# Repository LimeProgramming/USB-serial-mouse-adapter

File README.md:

# USB Serial Mouse Adapter
A USB to serial mouse adapter!

## About
This project came about when I got my hands on an old 486 based PC. Having never really dipped my toes into retro computing, I didn't have an old serial mouse on hand. A quick eBay searched revealed that the decent ones cost a nice chunk of change that I didn't feel they were worth. Another search on Vogons revealed that some mad lads out there made active PS/2 to serial adapters using various micro controllers.  
Out of curiosity I examined how these worked and thought "Why can't I do this with a Pi Pico and USB mouse?" which kicked off this project. 

I hope it sparks your interest!
-Lime

## Features
With this adapter you can convert a modern native USB mouse to a classic serial mouse. That's right, native USB! No cheating by secretly using PS/2 compatible mice.
Want to use an optical mouse on a 386 running Wolfenstein 3D? Well now you can! Want to use a wireless optical mouse on a 486 running Doom? Well you might be able to! (depending on the mouse)

**Supported Protocols:**
- Microsoft Two Button
- Logitech Three Button
- Microsoft Wheel

**Unsupported Protocols: (May change based on demand)**
- Mousesystems
- Sun
- MM

### KVM:
Support for use on KVMs has been added as of version 1.1.1. 
It works fine on my **one**, startech branded, KVM that I have test with. Given that TinyUSB is a bit picky, your results may vary.

## PCBs
There are two variants of the PCB available in the KiCad folder, Phat and Slim for your preference. The main circuit for both PCBs is the same so the firmware package will work on both PCBs. A full BOM for LCSC (except for header pins) is available in the Phat folder: [LCSC BOM](https://raw.githubusercontent.com/LimeProgramming/USB-serial-mouse-adapter/main/KiCad/Phat/BOM_LCSC.xls). For the Slim build you can omit the dip switches and reset switch (you will have to source an appropriate SMD reset switch).

### Building a PCB:

#### MAX232/3232 voltage selection:
The PCB has a jumper to select between 3.3v and 5v for the MAX chip. 
- If you're using a MAX232 then bridge 5v to the center pin and install all the resistors. The part listed in the [BOM](https://raw.githubusercontent.com/LimeProgramming/USB-serial-mouse-adapter/main/KiCad/Phat/BOM_LCSC.xls) is a MAX232 chip.
- If you're using a MAX3232 then bridge 3.3v to the center pin, bridge R4 and R3, and remove R1 and R2.

#### Board to Pico USB data connection:
The `TP2` and `TP3` testpoints on the board must be soldered to the corresponding `TP2` and `TP3` test points on the Pico, underneath the USB connector:

### Phat:

Also known as the original design.
This PCB is the version I had made with the mindset of it being the default/one and only. 
| Differences | Silkscreen | Description |
|:--:|:--:| :--:|
| Serial Pin Header | J1 | Intended to use with a serial breakout cable |
| USB Pin Header | J3 | Intended to be used with motherboard USB breakout cables |
| Dip Switches | SW1 | Quickly and easily configure the adapter |

#### Phat Cases:

### Slim:

Made for people be require the adapter to be as small as possible. Not much wider than the serial port itself. 

## Powering the device
### MicroUSB:

The easiest way to power the device would be to use the Pico's micro USB port. Be sure to use a USB power only cable or a wall power adapter otherwise it won't pick up the mouse.

**PLEASE NOTE:** Some "power only" USB cables have the data lines shorted together. You can test if this is the case by plugging the cable into the Pico and using a meter to check for continuity between `TP2` and `TP3` on the Pico. If there is continuity you have a cable like this. Cut the data lines on a normal USB cable as an option.
<br clear="left"/>

### Power-In Header:

Both the Phat and Slim PCB's feature an 5 volt power in header. You can use this creatively to power the adapter, even from the PC itself perhaps? Personally I'm connecting it to a wall power supply to give a more secure connection than MicroUSB.
<br clear="left"/>

### Other ways:
There is nothing stopping you from powering the device using a powered OTG cable or a hacked up USB extension lead. The device itself needs about 100 milliamps so as long as you get it that power, it'll run away happily!

## Configuration

The adapter has quite a few settings available and these settings are stored on micro controllers flash memory. 
It will remember your settings between uses and the same settings carry between different computers and even firmware upgrades (unless otherwise state in a changes log)

There are two primary ways of editing the settings of the USB-2-232

### Headers
The phat variant of the PCB includes headers in either of the form of dip switches or jumper headers. While not super configurable they do give quick access to some handy settings. The headers can be set while the micro controller is on with changes being applied in real-time or they can be set while the micro controller is off with changes being applied next time the controller is booted.

| Num | Setting |
|:--:|:--:|
| 1 | Three Button Logitech Protocol |
| 2 | MS Wheel Protocol |
| 3 | 75% Mouse Travel Modifier / Dip 3 + 4 for 25% |
| 4 | 50% Mouse Travel Modifier / Dip 3 + 4 for 25% |
| 5 | 7N2|
| 6 | 19200 Baud Rate|

### Serial Terminal

Both the phat and slim variants of the PCB support being configured via serial terminal. The serial terminal allows for more advanced configuration of the mouse adapter. Any additional settings added in a software update will be available here.
The serial terminal has been translated to German, images available in both German and English as default langauge.  

### Serial Terminal Options
+ Mouse Travel
    + List Config
            | List the current mouse travel settings
    + XY Travel 
            | XY mouse travel modifier 1% -> 200%
    + X Travel
             | X (Left and Right) mouse travel modifier 1% -> 200%
    + Y Travel 
            | Y ( Up and Down) mouse travel modifier 1% -> 200%
    + Invert X
            | Invert X (Left and Right) mouse movement.
    + Invert Y
            | Invert Y (Up and Down) mouse movement.
    + Movement Type
            | Set Movement Type. USB mice talk faster than serial mice, movement type decides what to do with the backlog between serial mouse updates.
        + Additive: 
                | Sum the mouse movement (Sensitive)
        + Average
                | Avg the mouse movement  (Insensitive)
        + Coast 
                | Send the mouse movement incrementally (Slippy)
    + Cosine Smoothing
            | Makes the cursor proportionally less sensitive at high speeds, leaving the movement mostly one to one at low speeds

+ Mouse Buttons
    + List Config
        | List the current mouse button settings
    + Swap Left and Right
        | Swap the left and right mouse buttons
    + Use Forward and Backward
        | Use the mouse forward and back buttons as alternative left and right buttons
    + Swap Forward and Backward
        | Swap forward and back buttons if they are being used as alternative left and right buttons
+ Serial Settings
    + List Config
        | List the current serial settings
    + Format
        | One stop bit (7N1) or two stop bits (7N2) 
    + Baud Rate
        | 1200 2400 4800 9600 19200 Baud Rates. Note you will need compatible mouse drivers.
     + Mouse Type
     | Microsoft 2 Button, Logitech Three Button or Microsoft Wheel mouse. Note: You may need to reconfigure your mouse driver upon change.
+ Firmware
    + Information | Information about the firmware
    + Language | Set the language of the settings terminal
    + Reset | Reset mouse settings back to default
    + List Default Settings | List the default settings of the adapter
+ Exit
    + Return to mouse mode

### Accessing the terminal
You can access the serial terminal in one of two ways:

#### Method 1: Serial Terminal Emulator
You can open a serial terminal emulator (like kermit) on the computer you have the mouse connected to, connect to the same com port the mouse driver is using and press the enter key.
```
Baud Rate: User Set
Data Bits: 7
Stop Bits: User Set
Parity: None
Flow Control: None
```
#### Method 2: USB to TTL
You can also connect the unused UART of the Pi Pico with a cheap USB to TTL device or even another Pico running the picoprobe firmware. Open your favorite serial terminal emulator (like putty) connect to the TTL device and tap the enter key. 
```
Baud Rate: 115200
Data Bits: 8
Stop Bits: 1
Parity: None
Flow Control: None
```
Connecting to the adapter in this way will allow you to change settings regardless of the adapter being connected to a PC or not. 
The unused UART of the pico can be accessed from the top two pins between the full size USB port of the PCB and the micro USB port of the Pico.

### Resetting the adapter
Forgot your settings and can't get the adapter working? Don't worry.
There are three different ways to reset the adapter:

#### --- Serial Terminal
As written above, you can reset the adapter back to default settings from the terminal. You can connect to the unused UART of the pico regardless of the settings of the mouse. 

#### --- Small Flat Head Screwdriver

**How To:**
1. Press a small flat head into the position shown above.
2. Power on the adapter and the Picos built-in LED will glow solid.
3. Hold the flat head in position for two or three seconds for the Picos LED to start blinking.
4. Once it is blinking, you can let go of the GPIO and press the reset button.
5. The adapter will boot up with default settings.
#### --- Nuke UF2
**How To:**
1. Download the [flash_nuke.uf2](https://datasheets.raspberrypi.com/soft/flash_nuke.uf2) file.
2. Connect the adapter to your PC using the microusb port built into the Pi Pico.
3. Hold Reset, then bootsel, then release reset then bootsel. This will make the Pico appear as a removable storage device. 
4. Drag the flash_nuke.uf2 file to the storage device. This will reset the flash the on the Pi Pico.
5. The Pico should reboot on its own and show up as a removable storage device again. If it doesn't, tap the reset button.
6. Download the latest firmware and drag that UF2 file to the storage device.
7. The adapter will boot up with default settings.

# Compiling the Firmware
The default mouse settings can be edited in `default_config.h` prior to compilation. You can use this to set the mouses default settings for your own configuration. 

The build environment is a normal PicoSDK setup, there are several guides out the for both Linux and Windows.  From experience the setup is easier in Linux. However there is one important thing you need to know:

**PicoSDK Version 1.5.1**
Previous Versions of this project required a customized version of TinyUSB, since then TinyUSB has implemented improved USB HUB and Hosting functions so the customized TinyUSB is no longer required. 
However, TinyUSB version 16 is recommended for the scroll wheel to work more reliably. 

# Known Issues
**USB Hubs**
Due to the pico having a USB 1.1 host or TinyUSB not using hubs correctly, this project struggles with hub compatibility. 
A hub which should work but I have not texted can be found here: https://www.olimex.com/Products/USB-Modules/USB-NeoHub/open-source-hardware 

Personally I use an amazon basics 4 port USB2.0 hub and it works perfectly.

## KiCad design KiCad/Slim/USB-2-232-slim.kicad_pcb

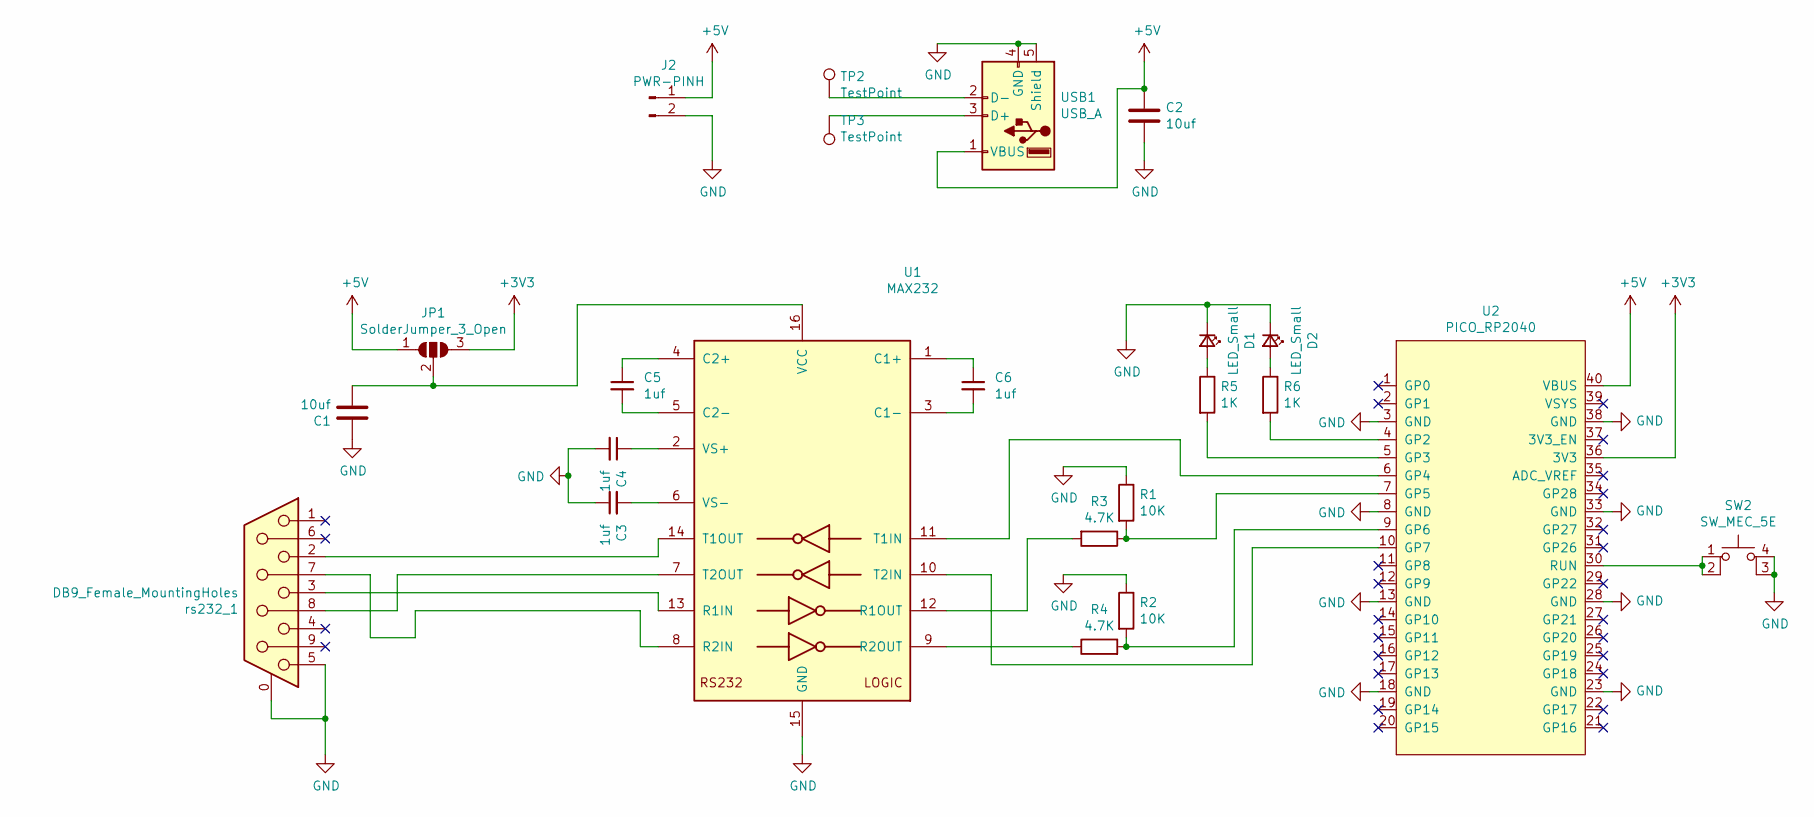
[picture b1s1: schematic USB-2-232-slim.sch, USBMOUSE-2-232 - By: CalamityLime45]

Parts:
C1, C2: 10uf; C_0805_2012Metric
C3, C4, C5, C6: 1uf; C_0805_2012Metric
D1, D2: LED_Small; LED_D3.0mm
J2: PWR-PINH; PinSocket_1x02_P2.54mm_Vertical
JP1: SolderJumper_3_Open; SolderJumper-3_P1.3mm_Open_Pad1.0x1.5mm_NumberLabels
R1, R2: 10K; R_0805_2012Metric
R3: 4.7K; R_0805_2012Metric_bridge
R4: 4.7K; R_0805_2012Metric_bridgeflip
R5, R6: 1K; R_0805_2012Metric
SW2: SW_MEC_5E; SMT_RESET_SW
TP2, TP3: TestPoint; TestPoint_Pad_1.5x1.5mm
U1: MAX232; max232_SMD
U2: PICO_RP2040; RPi_Pico_SMD_TH
USB1: USB_A; USB_A_Wuerth_614004134726_Horizontal
rs232_1: DB9_Female_MountingHoles; DSUB-9_Female_Horizontal_P2.77x2.84mm_EdgePinOffset7.70mm_H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

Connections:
+3V3: JP1.3 (B), U2.36 (3V3)
+5V: C2.1, J2.1, JP1.1 (A), U2.40 (VBUS), USB1.1 (VBUS)
GND: C1.1, C2.2, C3.1, C4.2, D1.1 (K), D2.1 (K), J2.2, R1.1, R2.1, SW2.3 (K), SW2.4 (A), U1.15 (GND), U2.3 (GND), U2.8 (GND), U2.13 (GND), U2.18 (GND), U2.23 (GND), U2.28 (GND), U2.33 (GND), U2.38 (GND), USB1.4 (GND), USB1.5 (Shield), rs232_1.0 (PAD), rs232_1.5
unnamed: C1.2, JP1.2 (C), U1.16 (VCC)
unnamed: C3.2, U1.6 (VS-)
unnamed: C4.1, U1.2 (VS+)
unnamed: C5.1, U1.4 (C2+)
unnamed: C5.2, U1.5 (C2-)
unnamed: C6.1, U1.1 (C1+)
unnamed: C6.2, U1.3 (C1-)
unnamed: D1.2 (A), R5.1
unnamed: D2.2 (A), R6.1
unnamed: R1.2, R3.1, U2.7 (GP5)
unnamed: R2.2, R4.2, U2.9 (GP6)
unnamed: R3.2, U1.12 (R1OUT)
unnamed: R4.1, U1.9 (R2OUT)
unnamed: R5.2, U2.5 (GP3)
unnamed: R6.2, U2.4 (GP2)
unnamed: SW2.1, SW2.2, U2.30 (RUN)
unnamed: TP2.1, USB1.2 (D-)
unnamed: TP3.1, USB1.3 (D+)
unnamed: U1.7 (T2OUT), rs232_1.8
unnamed: U1.8 (R2IN), rs232_1.7
unnamed: U1.10 (T2IN), U2.10 (GP7)
unnamed: U1.11 (T1IN), U2.6 (GP4)
unnamed: U1.13 (R1IN), rs232_1.3
unnamed: U1.14 (T1OUT), rs232_1.2

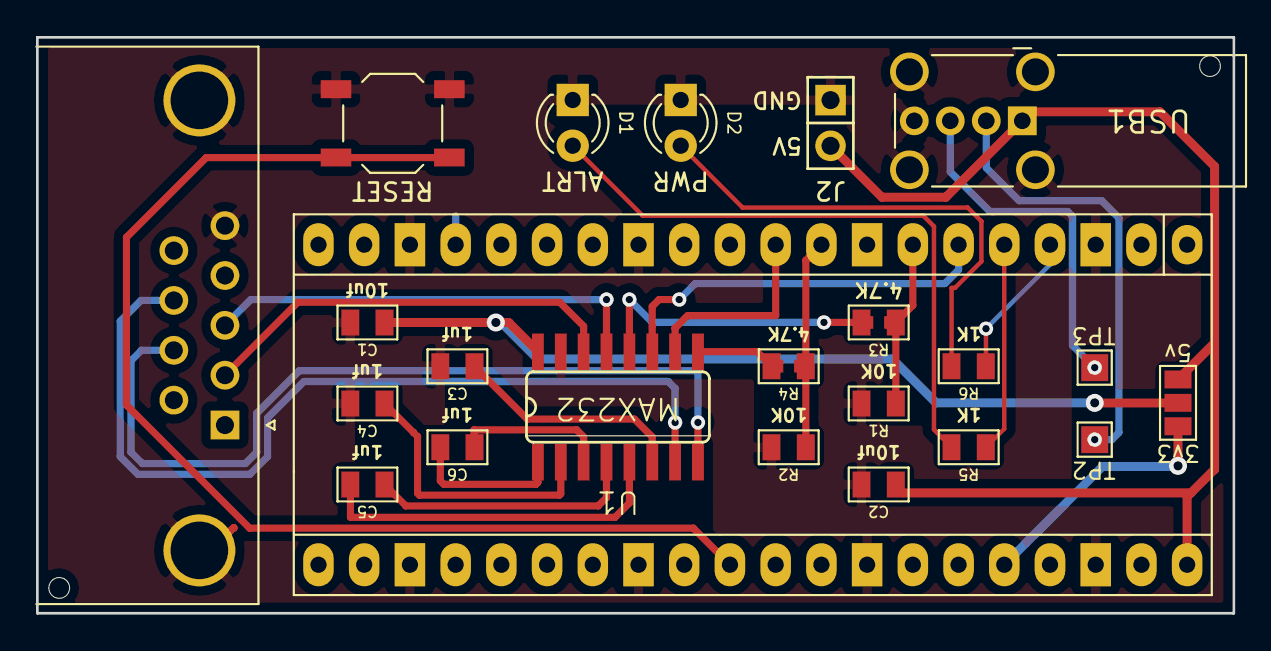
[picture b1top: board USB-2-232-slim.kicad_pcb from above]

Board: 2 copper layers, 66.5 x 32.0 mm, 23 parts (0 on the bottom side), 27 nets.

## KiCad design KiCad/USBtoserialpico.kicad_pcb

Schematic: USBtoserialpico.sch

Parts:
C1, C2, C3, C5: 1uf; C_1206_3216Metric
C4, C6: 10uf; C_1206_3216Metric
D1, D2: LED_Small; LED_D3.0mm
J1: Conn_01x04_Male; Serial_PinSocket_1x04_P2.54mm
J2: Conn_01x02_Male; PinSocket_1x02_P2.54mm_Vertical
J3: Conn_01x05_Male; PinSocket_1x05_P2.54mm_Vertical
JP1: SolderJumper_3_Open; SolderJumper-3_P1.3mm_Open_Pad1.0x1.5mm_NumberLabels
R1, R2: 3K; R_1206_3216Metric
R3, R4: R; R_1206_3216Metric
RB1: 1.5K; R_1206_3216Metric_bridge
RB2: 1.5K; R_1206_3216Metric
SW1: SW_DIP_x06; SW_DIP_SPSTx06_Slide_9.78x17.42mm_W7.62mm_P2.54mm
SW2: SW_MEC_5E; SW_PUSH_6mm
TP1, TP2: TestPoint; TestPoint_Pad_1.5x1.5mm
U1: MAX232; max232_SMD
U2: PICO_RP2040; RPi_Pico_SMD_TH
USB1: USB_A; USB_A_Wuerth_614004134726_Horizontal
rs232_1: DB9_Female_MountingHoles; DSUB-9_Male_Horizontal_P2.77x2.84mm_EdgePinOffset7.70mm_Hou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

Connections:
+5V: C6.1, J2.1, J3.1, JP1.1 (A), U2.40 (VBUS), USB1.1 (VBUS)
GND: C1.2, C2.1, C4.1, C6.2, J1.4, J2.2, J3.4, J3.5, R1.1, R2.1, R3.1, R4.1, SW1.7, SW1.8, SW1.9, SW1.10, SW1.11, SW1.12, SW2.3 (K), SW2.4 (A), U1.15 (GND), U2.3 (GND), U2.8 (GND), U2.13 (GND), U2.18 (GND), U2.23 (GND), U2.28 (GND), U2.33 (GND), U2.38 (GND), USB1.4 (GND), USB1.5 (Shield), rs232_1.5
unnamed: C1.1, U1.2 (VS+)
unnamed: C2.2, U1.6 (VS-)
unnamed: C3.1, U1.4 (C2+)
unnamed: C3.2, U1.5 (C2-)
unnamed: C4.2, JP1.2 (C), U1.16 (VCC)
unnamed: C5.1, U1.1 (C1+)
unnamed: C5.2, U1.3 (C1-)
unnamed: D1.1 (K), R3.2
unnamed: D1.2 (A), U2.5 (GP3)
unnamed: D2.1 (K), R4.2
unnamed: D2.2 (A), U2.4 (GP2)
unnamed: J1.1, U1.8 (R2IN), rs232_1.7
unnamed: J1.2, U1.13 (R1IN), rs232_1.2
unnamed: J1.3, U1.14 (T1OUT), rs232_1.3
unnamed: J3.2, TP1.1, USB1.2 (D-)
unnamed: J3.3, TP2.1, USB1.3 (D+)
unnamed: JP1.3 (B), U2.36 (3V3)
unnamed: R1.2, RB1.1, U2.7 (GP5)
unnamed: R2.2, RB2.2, U2.9 (GP6)
unnamed: RB1.2, U1.12 (R1OUT)
unnamed: RB2.1, U1.9 (R2OUT)
unnamed: SW1.1, U2.12 (GP9)
unnamed: SW1.2, U2.14 (GP10)
unnamed: SW1.3, U2.15 (GP11)
unnamed: SW1.4, U2.16 (GP12)
unnamed: SW1.5, U2.17 (GP13)
unnamed: SW1.6, U2.19 (GP14)
unnamed: SW2.1, SW2.2, U2.30 (RUN)
unnamed: U1.11 (T1IN), U2.6 (GP4)

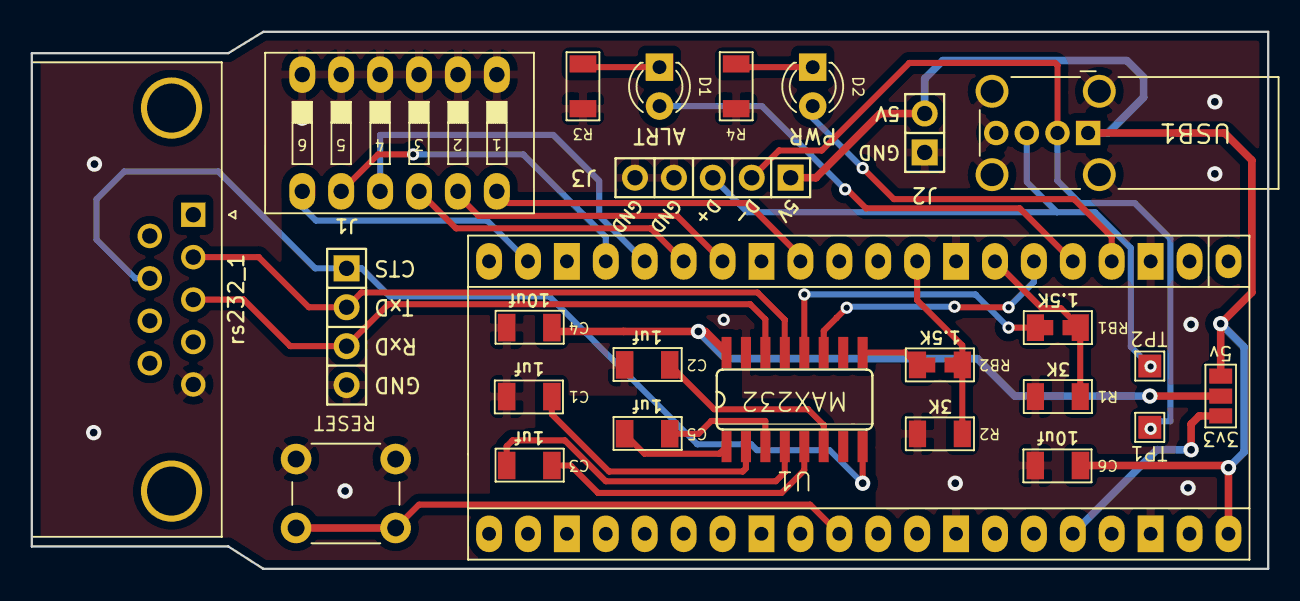
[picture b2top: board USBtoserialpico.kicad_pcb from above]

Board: 2 copper layers, 80.7 x 35.1 mm, 26 parts (0 on the bottom side), 31 nets.

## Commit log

2021-11-11 init commit
    yeah, it's the init commit.
2021-11-13 converted tabs to spaces
2021-11-15 KiCad Files Upload
2021-11-15 images upload
2021-11-15 readme
2021-11-15 Added Firmware Folder
2021-11-15 Update
    Changed the function that sends data over serial to an IRQ from a loop. What I was using to time things before died after an hour.
2021-11-15 fixed some small mistakes in the pcb
    I forgot to give the max232 a connection to ground.
2021-11-17 Updated KiCad Files
2021-12-19 bin update
2021-12-31 PCBv2
    Fixed the silkscreen for J1 and fixed the crossed traces on serial connector.
    Moved some traces around to make it look nicer and changed the PFP logo so hopefully JLC can't feck it up.
2021-12-31 PCB images
    turns out github doesn't like webp for no reason
2022-01-01 slimline PCB
    Made as an answer to people asking for this project without dipswitches. I decided to remove the usb pin header and the serial pin header while I was at it.
2022-01-01 moved phat pcb images
2022-01-01 Fixed misplaced silkscreen
2022-01-06 add images
2022-01-14 external case update
2022-01-15 Internal phat case
2022-01-16 image
2022-01-16 images
2022-01-16 Initial Release Firmware
    I think we're ready to really get moving.
    Version 1.0 firmware release.
2022-03-23 Release of Version 1.1.1
2022-05-01 Version 1.2.2 Release
    Added Changelog.MD file, read that
2022-06-27 Update 1.3.2
    Bug fix. It saved your settings but never loaded them on reboot.
    no flash nuke required from version 1.2.2
2022-07-24 Modified Drivers added
    Compiled from source
2024-06-09 Added LCSC BOM and updated README.md
2024-06-09 fixed capitalization
2024-06-24 added 3/5v bridging instructions
2024-06-25 Added TP2/3 info
2024-06-25 Added modified Windows 9x serial mouse drivers
    read the readme's thanks.
2024-06-26 "power only" USB cable note. removed hard coding of Pico SDK location
2024-07-03 Fix wheel mouse 3rd button bit
2024-07-07 fixes from LimeProgramming
2024-07-07 Remove Customised TinyUSB + preparing for updated PicoSDK
2024-07-08 Update
    Add support for updated TinyUSB version to hopefully make it work better.
2024-08-07 more Drivers
    Added more drivers, MS-Dos, Win3.1, intellipoint and another version of win98se, I've included the Byte location of the serial latch divisor where possible.
